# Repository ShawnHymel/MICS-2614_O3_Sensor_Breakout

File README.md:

O3_Sensor_Breakout
==================

Breakout board for the MiCS-2614 O3 sensor.

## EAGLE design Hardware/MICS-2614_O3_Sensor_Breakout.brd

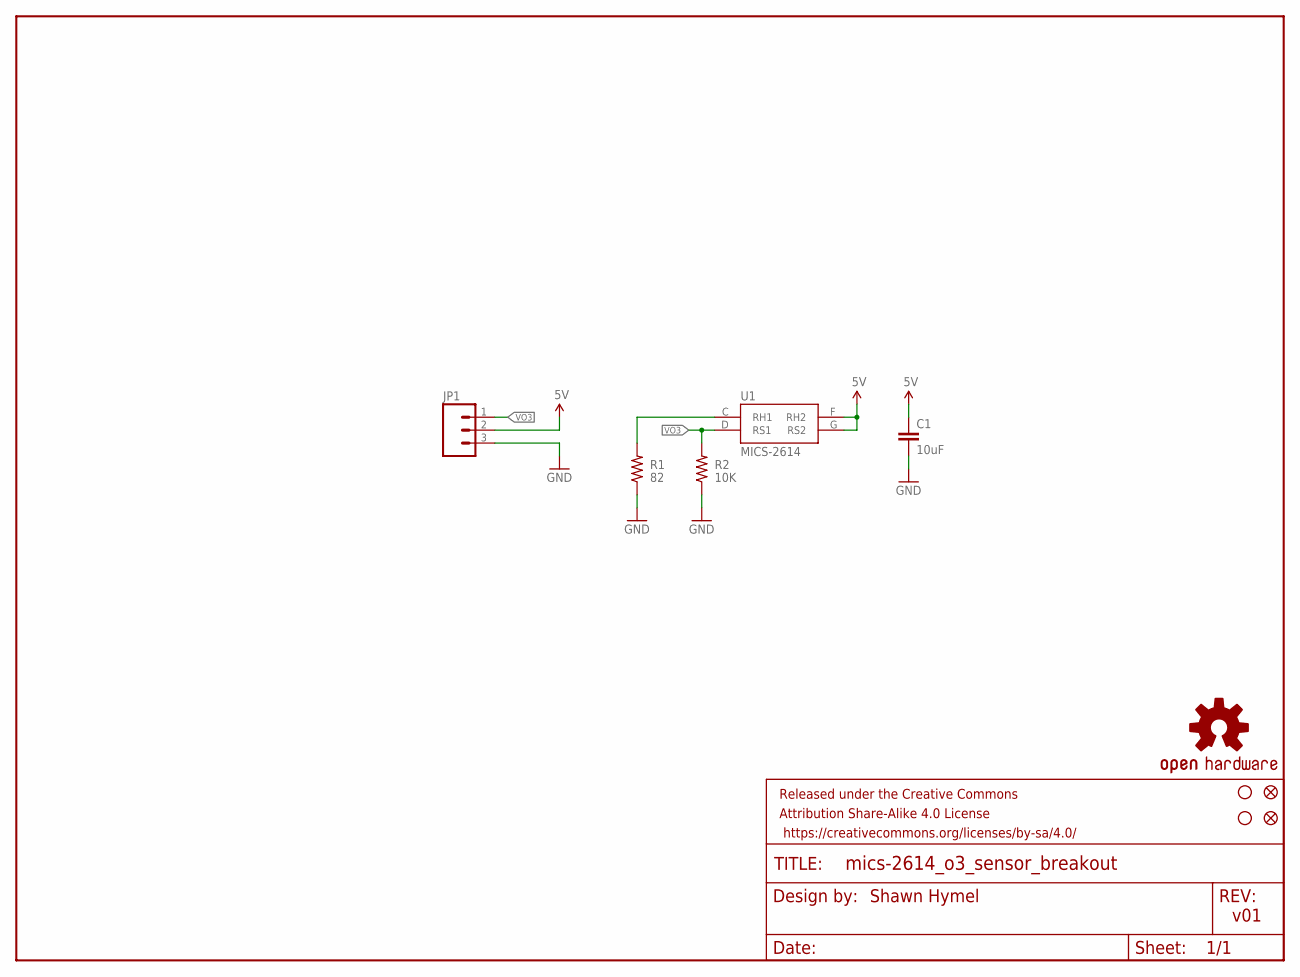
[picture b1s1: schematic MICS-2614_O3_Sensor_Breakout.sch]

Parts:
C1: 10uF; 0805
FID1, FID2: FIDUCIAL1X2; FIDUCIAL-1X2
FRAME1: FRAME-LETTER; CREATIVE_COMMONS
JP1: M03LOCK; 1X03_LOCK
LOGO1: OSHW-LOGOS; OSHW-LOGO-S
R1: 82; 0805
R2: 10K; 0603-RES
STANDOFF3, STANDOFF5: STAND-OFF
U1: MICS-2614; MICS_10-SMD

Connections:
5V: C1.1, JP1.2, U1.F (RH2), U1.G (RS2)
GND: C1.2, JP1.3, R1.1, R2.1
unnamed: R1.2, U1.C (RH1)
VO3: JP1.1, R2.2, U1.D (RS1)

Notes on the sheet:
Shawn Hymel
v01

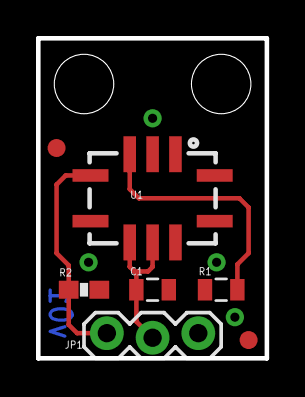
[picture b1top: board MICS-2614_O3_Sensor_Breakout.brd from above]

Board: 2 copper layers, 12.7 x 17.8 mm, 11 parts (1 on the bottom side), 4 nets.

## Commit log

2014-10-16 Created schematic
2014-10-17 v01 board layout complete. Ready for prototypes.
2014-10-17 Moved top via to line up with OSHW logo.
2014-10-17 Moved JP1 label
2014-10-21 Added BOM
2014-12-22 Added test Arduino code and photos.

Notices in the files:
parts and their libraries:
SparkFun-Aesthetics: Licensing: Creative Commons ShareAlike 4.0 International - https://creativecommons.org/licenses/by-sa/4.0
SparkFun-Aesthetics: Released under the Creative Commons Attribution Share-Alike 4.0 License
SparkFun-Aesthetics: https://creativecommons.org/licenses/by-sa/4.0
